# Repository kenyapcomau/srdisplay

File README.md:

# Shift register display

These are the Kicad design files for the shift register display described in my [Hackaday project](https://hackaday.io/project/168654-an-uninnovative-linear-led-display)

## Versioning

Working release January 2020

## Notes

srdisplay.ino is an Arduino sketch to test the display.

At assembly time you should choose between sourcing current to the LEDs by installing the Source/Sink soldered jumper. If sinking is chosen, the LEDs should be installed in reverse polarity to the silkscreen legend.

If you do not wish to drive /OE for PWM brightness control from the controller, you should jumper it to ground.

## Authors

* **Ken Yap**

## License

See the [LICENSE](LICENSE.md) file for license rights and limitations (MIT).

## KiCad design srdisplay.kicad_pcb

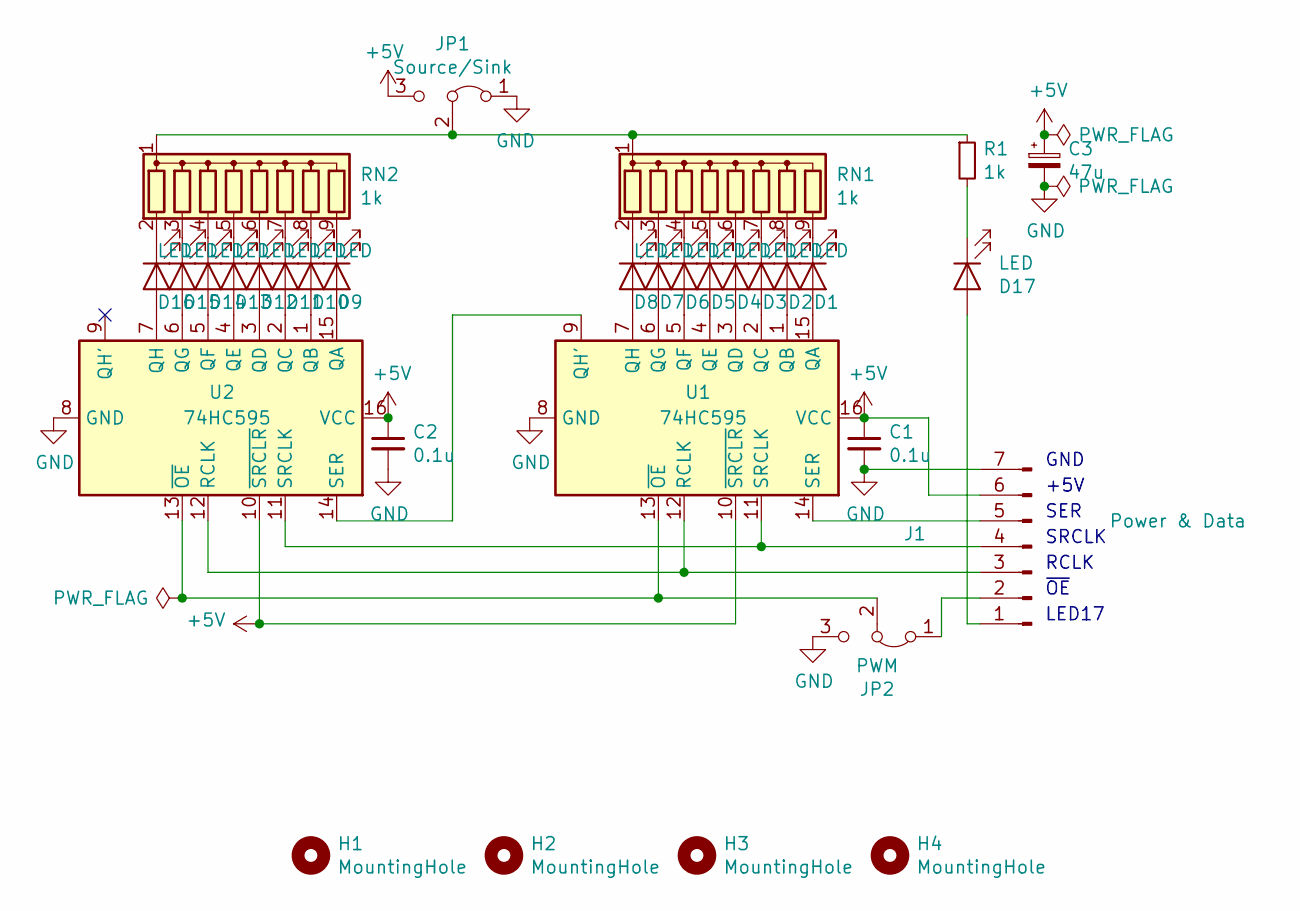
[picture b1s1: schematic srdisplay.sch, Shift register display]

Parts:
C1, C2: 0.1u; C_Rect_L7.0mm_W2.0mm_P5.00mm
C3: 47u; CP_Radial_D5.0mm_P2.50mm
D1, D2, D3, D4, D5, D6, D7, D8, D9, D10, D11, D12, D13, D14, D15, D16, D17: LED; LED_D3.0mm
H1, H2, H3, H4: MountingHole; MountingHole_3mm_Pad
J1: Power & Data; PinHeader_1x07_P2.54mm_Horizontal
JP1: Source/Sink; 1X03
JP2: PWM; PinHeader_1x03_P2.54mm_Vertical
R1: 1k; R_Axial_DIN0207_L6.3mm_D2.5mm_P10.16mm_Horizontal
RN1, RN2: 1k; R_Array_SIP9
U1, U2: 74HC595; DIP-16_W7.62mm

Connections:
+5V: C1.1, C2.1, C3.1, J1.6, JP1.3 (B), U1.10 (~SRCLR), U1.16 (VCC), U2.10 (~SRCLR), U2.16 (VCC)
GND: C1.2, C2.2, C3.2, J1.7, JP1.1 (A), JP2.3 (B), U1.8 (GND), U2.8 (GND)
unnamed: D1.1 (K), RN1.9 (R8)
unnamed: D1.2 (A), U1.15 (QA)
unnamed: D2.1 (K), RN1.8 (R7)
unnamed: D2.2 (A), U1.1 (QB)
unnamed: D3.1 (K), RN1.7 (R6)
unnamed: D3.2 (A), U1.2 (QC)
unnamed: D4.1 (K), RN1.6 (R5)
unnamed: D4.2 (A), U1.3 (QD)
unnamed: D5.1 (K), RN1.5 (R4)
unnamed: D5.2 (A), U1.4 (QE)
unnamed: D6.1 (K), RN1.4 (R3)
unnamed: D6.2 (A), U1.5 (QF)
unnamed: D7.1 (K), RN1.3 (R2)
unnamed: D7.2 (A), U1.6 (QG)
unnamed: D8.1 (K), RN1.2 (R1)
unnamed: D8.2 (A), U1.7 (QH)
unnamed: D9.1 (K), RN2.9 (R8)
unnamed: D9.2 (A), U2.15 (QA)
unnamed: D10.1 (K), RN2.8 (R7)
unnamed: D10.2 (A), U2.1 (QB)
unnamed: D11.1 (K), RN2.7 (R6)
unnamed: D11.2 (A), U2.2 (QC)
unnamed: D12.1 (K), RN2.6 (R5)
unnamed: D12.2 (A), U2.3 (QD)
unnamed: D13.1 (K), RN2.5 (R4)
unnamed: D13.2 (A), U2.4 (QE)
unnamed: D14.1 (K), RN2.4 (R3)
unnamed: D14.2 (A), U2.5 (QF)
unnamed: D15.1 (K), RN2.3 (R2)
unnamed: D15.2 (A), U2.6 (QG)
unnamed: D16.1 (K), RN2.2 (R1)
unnamed: D16.2 (A), U2.7 (QH)
unnamed: D17.1 (K), R1.2
unnamed: D17.2 (A), J1.1
unnamed: J1.2, JP2.1 (A)
unnamed: J1.3, U1.12 (RCLK), U2.12 (RCLK)
unnamed: J1.4, U1.11 (SRCLK), U2.11 (SRCLK)
unnamed: J1.5, U1.14 (SER)
unnamed: JP1.2 (C), R1.1, RN1.1 (common), RN2.1 (common)
unnamed: JP2.2 (C), U1.13 (~OE), U2.13 (~OE)
unnamed: U1.9 (QH'), U2.14 (SER)

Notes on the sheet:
GND
+5V
SER
SRCLK
RCLK
LED17
~OE~

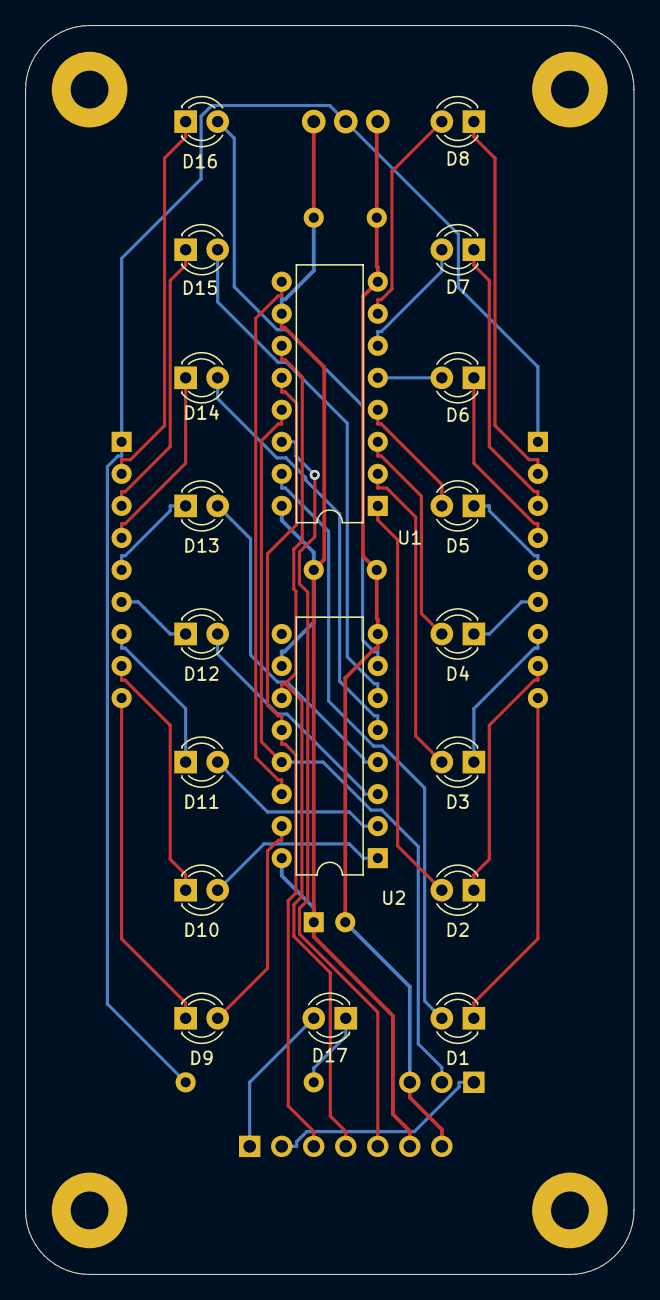
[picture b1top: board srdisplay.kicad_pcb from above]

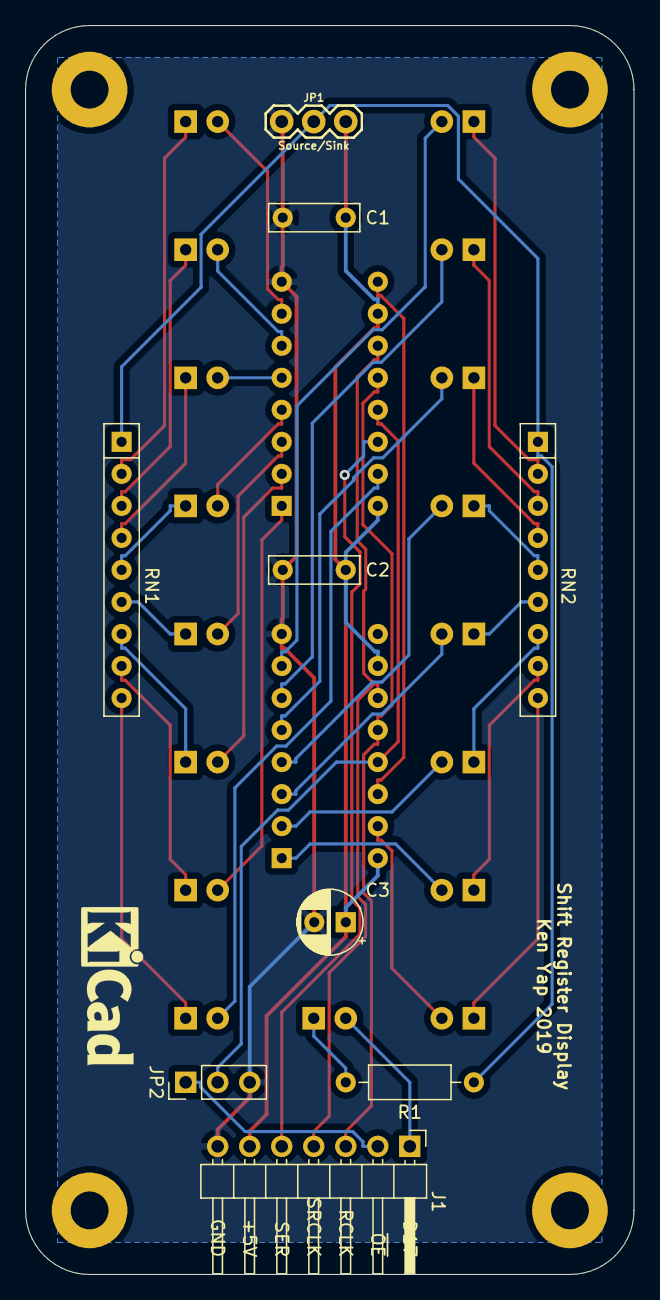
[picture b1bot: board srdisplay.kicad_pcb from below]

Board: 2 copper layers, 48.3 x 99.1 mm, 32 parts (9 on the bottom side), 43 nets.

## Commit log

2020-01-02 Working release
2021-09-19 #define options for 24 hour clock display, and inverted polarity for sinking current through LEDs
